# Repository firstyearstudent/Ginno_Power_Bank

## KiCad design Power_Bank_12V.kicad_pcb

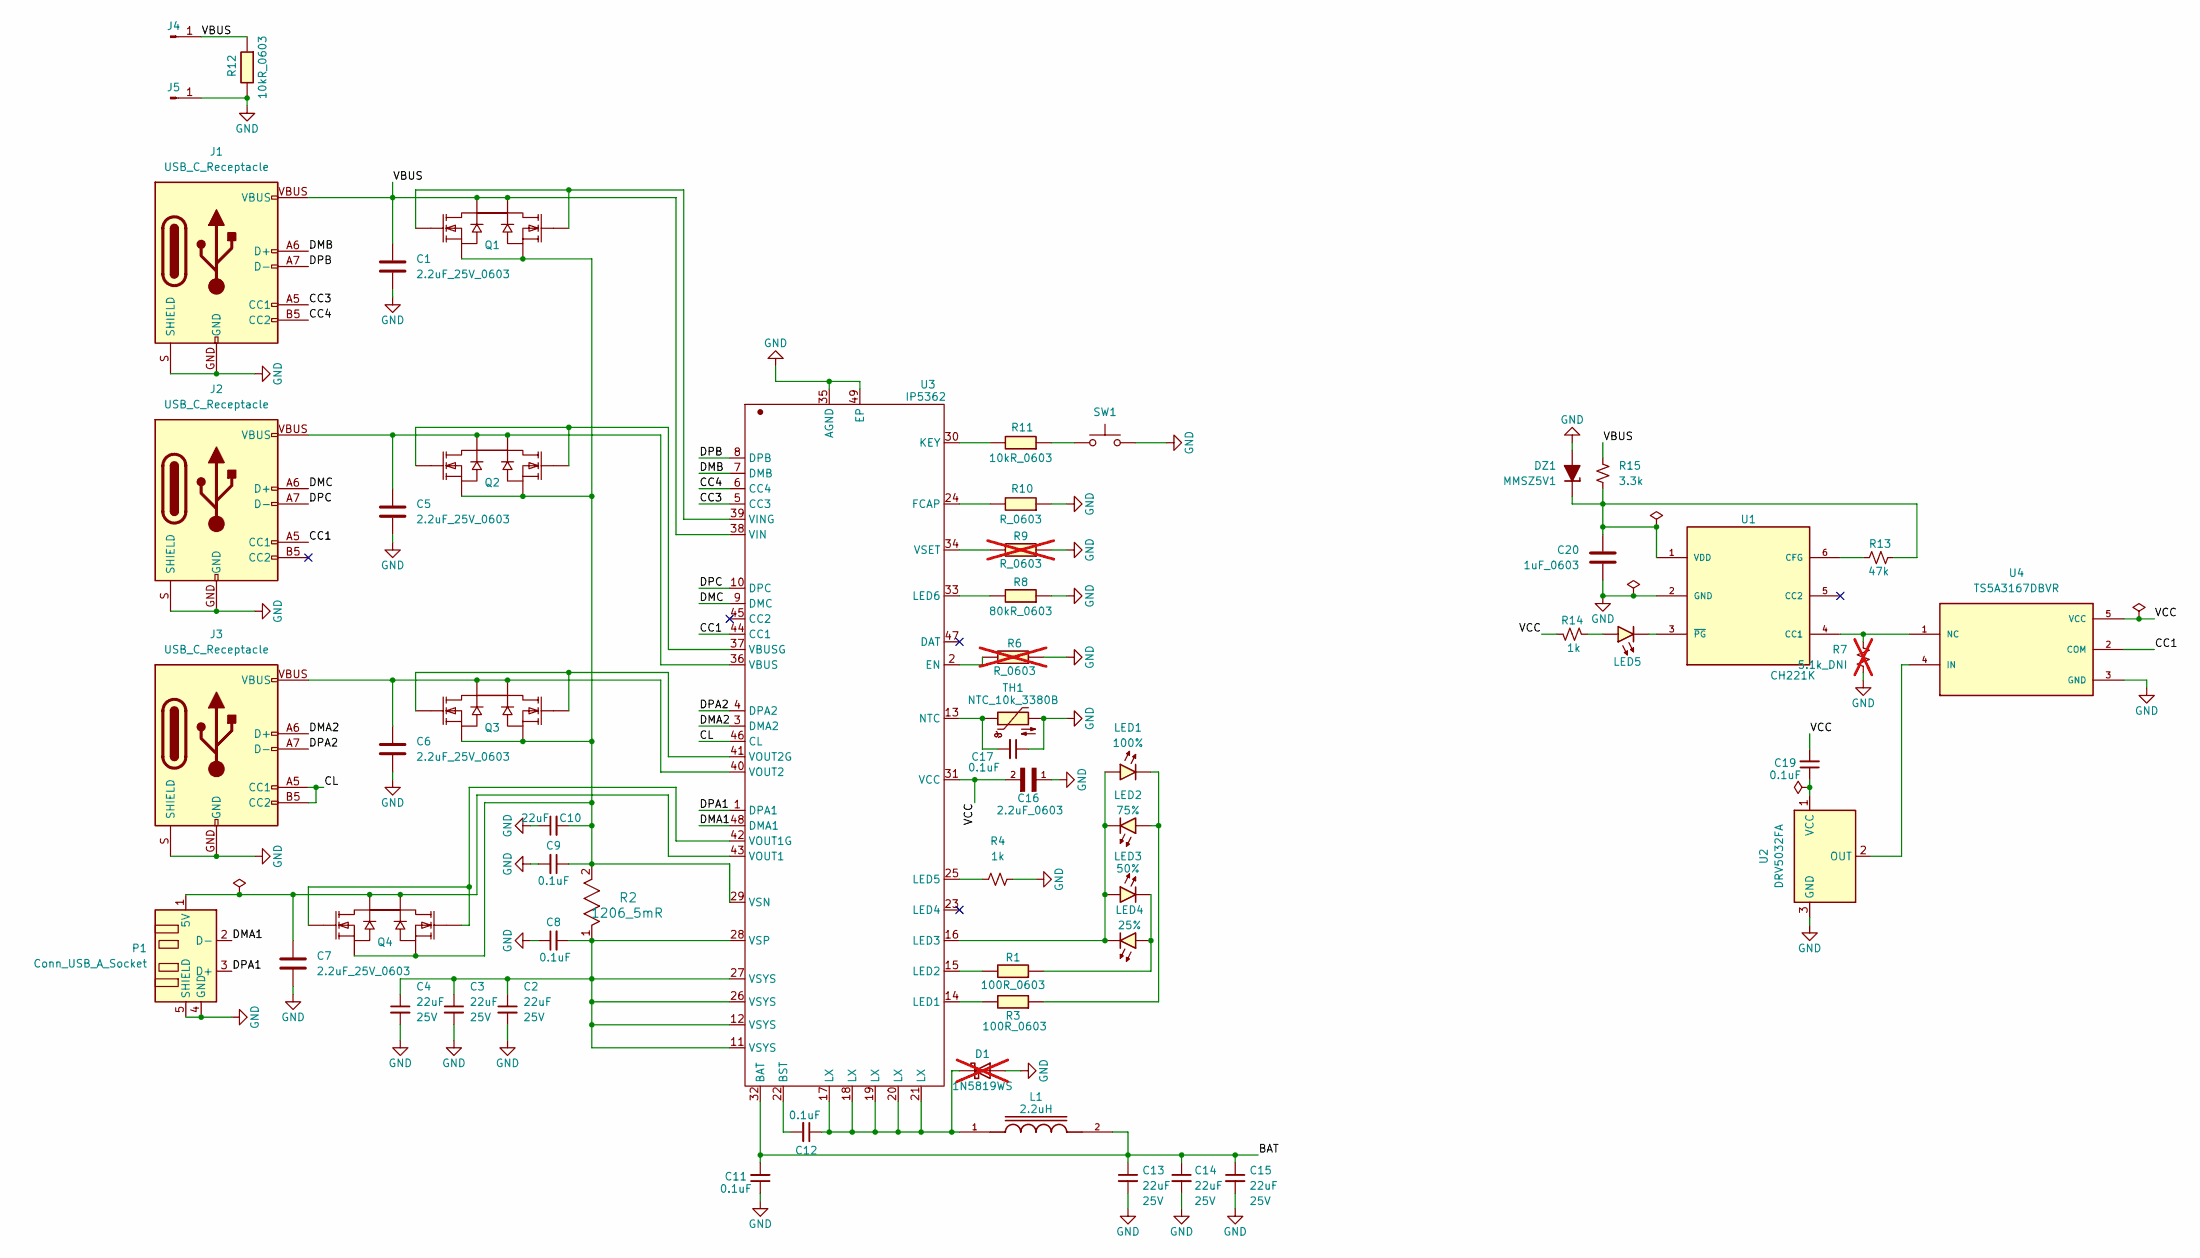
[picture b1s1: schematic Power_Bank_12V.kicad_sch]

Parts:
C1, C5, C6, C7: 2.2uF_25V_0603; C_0603_1608Metric
C2, C3, C4, C13, C14, C15: 22uF; C_0805_2012Metric; Voltage 25V
C8, C9, C11, C12, C17, C19: 0.1uF; C_0603_1608Metric
C10: 22uF; C_0805_2012Metric
C16: 2.2uF_0603; CAPC1608X90
C20: 1uF_0603; C_0603_1608Metric
D1: 1N5819WS; D_SOD-323; not fitted
DZ1: MMSZ5V1; D_SOD-123
J1, J2, J3: USB_C_Receptacle; USB-C_16
J4, J5: Conn_01x01_Pin; PinHeader_1x01_P2.54mm_Vertical
L1: 2.2uH; IND_F1F3-1004T-2R2M; PARTREV 1
LED1, LED5: 100%; LED_0805_2012Metric
LED2: 75%; LED_0805_2012Metric
LED3: 50%; LED_0805_2012Metric
LED4: 25%; LED_0805_2012Metric
P1: Conn_USB_A_Socket; Conn_USB_A_Socket_AdamTech_USB-A-S-RA-TSMT
Q1, Q2, Q3, Q4: SOT-23-6_L2.9-W1.6-P0.95-LS2.8-BR
R1, R3: 100R_0603; R_0603
R2: 1206_5mR; RES_VISHAY_WSLP1206_VIS
R4, R14: 1k; R_0603_1608Metric
R6, R9: R_0603; not fitted
R7: 5.1k_DNI; R_0603_1608Metric; not fitted
R8: 80kR_0603; R_0603
R10: R_0603
R11, R12: 10kR_0603; R_0603
R13: 47k; R_0603_1608Metric
R15: 3.3k; R_0603_1608Metric
SW1: Switch_Tactile_CnK; Button_CnK_PTS636.0_6x3.5mm
TH1: NTC_10k_3380B; R_1206
U1: CH221K; SOT95P280X120-6N; PARTREV 2.1
U2: DRV5032FA; SOT-23
U3: IP5362; UQFN-48_L6.0-W6.0-P0.40-BL-EP4.4
U4: TS5A3167DBVR; SOT95P280X145-5N; PARTREV D

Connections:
/BAT: C11.2, C13.1, C14.1, C15.1, L1.2, U3.32 (BAT)
/CC1: J2.A5 (CC1), U3.44 (CC1), U4.2 (COM)
/CC3: J1.A5 (CC1), U3.5 (CC3)
/CC4: J1.B5 (CC2), U3.6 (CC4)
/CL: J3.A5 (CC1), J3.B5 (CC2), U3.46 (CL)
/DMA1: P1.2 (D-), U3.48 (DMA1)
/DMA2: J3.A6 (D+), J3.B6 (D+), U3.3 (DMA2)
/DMB: J1.A6 (D+), J1.B6 (D+), U3.7 (DMB)
/DMC: J2.A6 (D+), J2.B6 (D+), U3.9 (DMC)
/DPA1: P1.3 (D+), U3.1 (DPA1)
/DPA2: J3.A7 (D-), J3.B7 (D-), U3.4 (DPA2)
/DPB: J1.A7 (D-), J1.B7 (D-), U3.8 (DPB)
/DPC: J2.A7 (D-), J2.B7 (D-), U3.10 (DPC)
/VBUS: C1.1, J1.VBUS, J4.1 (Pin_1_1), Q1.2 (D1/D2), Q1.5 (D1/D2), R12.2, R15.2, U3.38 (VIN)
/VCC: C16.2, C19.2, R14.2, U3.31 (VCC), U4.5 (VCC)
GND: C1.2, C2.2, C3.2, C4.2, C5.2, C6.2, C7.2, C8.1, C9.2, C10.1, C11.1, C13.2, C14.2, C15.2, C16.1, C17.1, C20.2, D1.2 (A), DZ1.2 (A), J1.GND, J1.S (SHIELD), J2.GND, J2.S (SHIELD), J3.GND, J3.S (SHIELD), J5.1 (Pin_1_1), P1.4 (GND), P1.5 (SHIELD), R4.2, R6.2, R7.1, R8.2, R9.2, R10.2, R12.1, SW1.2, TH1.2, U1.2 (GND), U2.3 (GND), U3.35 (AGND), U3.49 (EP), U4.3 (GND)
unnamed: C12.1, D1.1 (K), L1.1, U3.17 (LX), U3.18 (LX), U3.19 (LX), U3.20 (LX), U3.21 (LX)
unnamed: C20.1, DZ1.1 (K), R13.2, R15.1, U1.1 (VDD)
unnamed: LED1.2 (A), LED2.1 (K), LED3.2 (A), LED4.1 (K), U3.16 (LED3)
unnamed: LED1.1 (K), LED2.2 (A), R3.2
unnamed: LED3.1 (K), LED4.2 (A), R1.2
unnamed: LED5.2 (A), R14.1
unnamed: LED5.1 (K), U1.3 (~PG)
unnamed: C7.1, P1.1 (5V), Q4.2 (D1/D2), Q4.5 (D1/D2), U3.43 (VOUT1)
unnamed: Q1.4 (G2), Q1.6 (G1), U3.39 (VING)
unnamed: C9.1, C10.2, Q1.1 (S1), Q1.3 (S2), Q2.1 (S1), Q2.3 (S2), Q3.1 (S1), Q3.3 (S2), Q4.1 (S1), Q4.3 (S2), R2.2, U3.29 (VSN)
unnamed: Q2.4 (G2), Q2.6 (G1), U3.37 (VBUSG)
unnamed: Q3.4 (G2), Q3.6 (G1), U3.41 (VOUT2G)
unnamed: Q4.4 (G2), Q4.6 (G1), U3.42 (VOUT1G)
unnamed: R11.2, SW1.1
unnamed: R7.2, U1.4 (CC1), U4.1 (NC)
unnamed: R13.1, U1.6 (CFG)
unnamed: U2.2 (OUT), U4.4 (IN)
unnamed: C19.1, U2.1 (VCC)
unnamed: C12.2, U3.22 (BST)
unnamed: R6.1, U3.2 (EN)
unnamed: R10.1, U3.24 (FCAP)
unnamed: R11.1, U3.30 (KEY)
unnamed: R3.1, U3.14 (LED1)
unnamed: R1.1, U3.15 (LED2)
unnamed: R4.1, U3.25 (LED5)
unnamed: R8.1, U3.33 (LED6)
unnamed: C17.2, TH1.1, U3.13 (NTC)
unnamed: C5.1, J2.VBUS, Q2.2 (D1/D2), Q2.5 (D1/D2), U3.36 (VBUS)
unnamed: C6.1, J3.VBUS, Q3.2 (D1/D2), Q3.5 (D1/D2), U3.40 (VOUT2)
unnamed: R9.1, U3.34 (VSET)
unnamed: C2.1, C3.1, C4.1, C8.2, R2.1, U3.11 (VSYS), U3.12 (VSYS), U3.26 (VSYS), U3.27 (VSYS), U3.28 (VSP)

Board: 2 copper layers, 57 parts (0 on the bottom side), 47 nets, no tracks yet.
